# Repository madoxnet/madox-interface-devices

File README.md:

Madox-Ergonomic-Trackball
Mouse-Ergonomics-Test

|Function|Component|Module|
|---|---|---|
|Processing|ARM Cortex M4F|Adafruit Feather nRF52 Bluefruit LE |
|Power source|1000 mAh Lithium Polymer||
|Optical Sensing|Avago ADNS-9800||
|Optical Lens|Avago ADNS-6190-002||

## Design Parameters
|Parameter|Min|Nom|Max|
|---|---|---|---|
|Sensing distance|2.18mm|2.4mm|2.62|
|Bearing diameter||3mm||
|Trackball diameter||40mm||
|Handedness||Right||

## Controls
- Left Mouse Button
- Right Mouse Button
- Scroll Wheel
- Scroll Wheel Centre Mouse
- Power Switch
- ~~Scroll Wheel left right = Ctrl Tab / Ctrl Shift Tab?~~

## Target Specifications
|Parameter|Min|
|---|---|
|Ball diameter|40mm|
|Ball Material|Tiger's Eye|
|Ball Suspension|3mm Silicon Nitride (Si<sub>3</sub>N<sub>4</sub>) Round Bearings in Polycprolactone casing |
|Construction|Acrylonitrile butadiene styrene|
|Tracking Technology|Laser Optical Sensing|
|Tracking Resolution|Up to 8200 counts per inch|
|Tracking Speed|Up to 150 inches per second|

<https://en.wikipedia.org/wiki/Tiger%27s_eye>
<https://en.wikipedia.org/wiki/Silicon_nitride>

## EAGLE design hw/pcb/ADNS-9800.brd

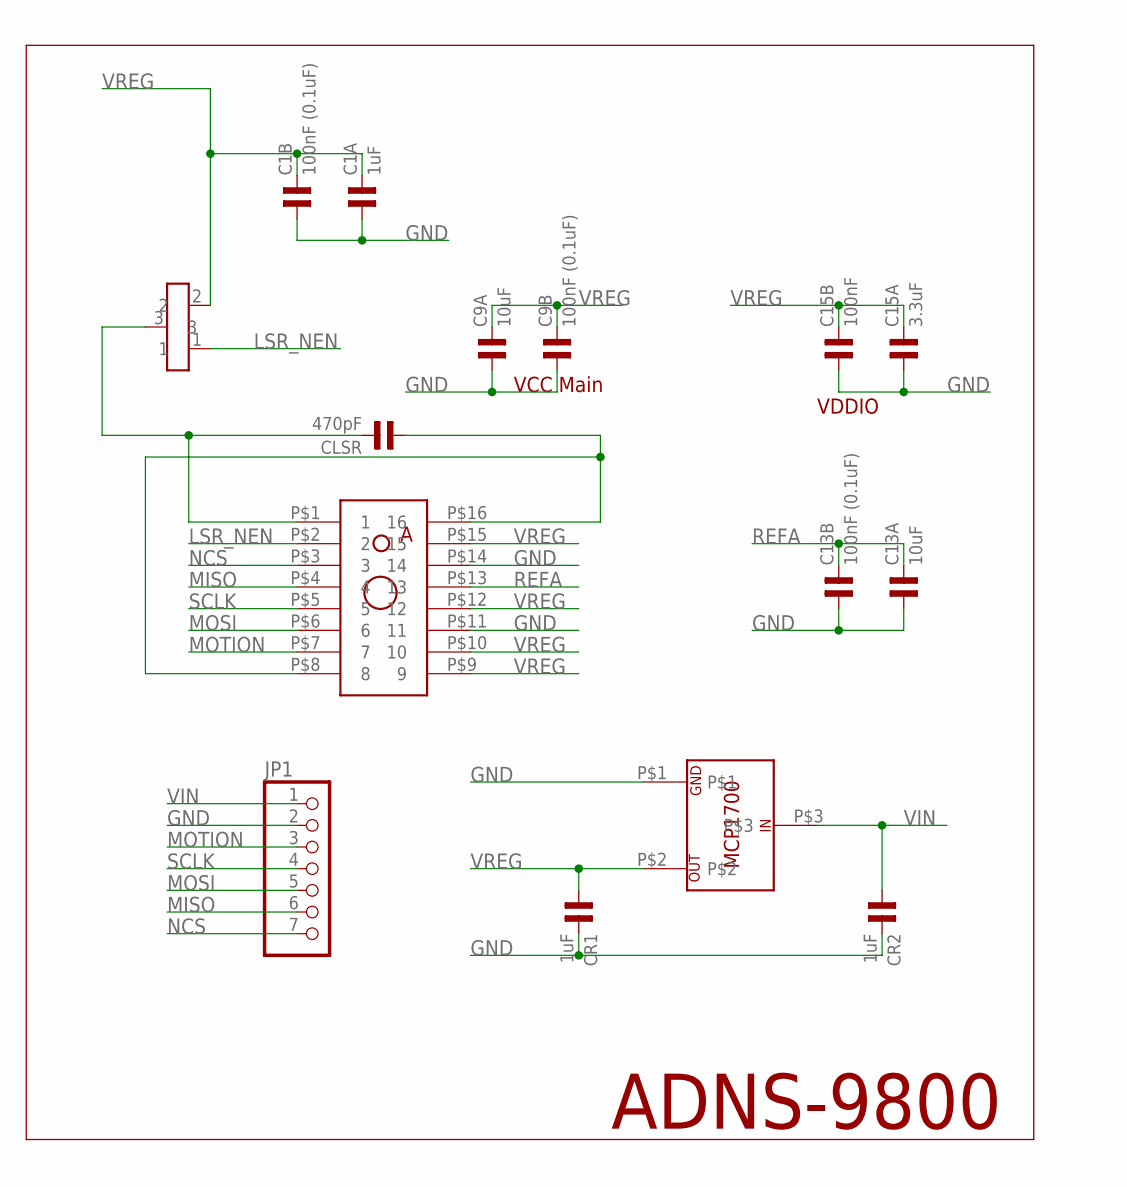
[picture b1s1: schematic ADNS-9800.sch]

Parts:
C1A: 1uF; 0603
C1B, C9B, C13B: 100nF (0.1uF); 0603
C9A, C13A: 10uF; 0603
C15A: 3.3uF; 0603
C15B: 100nF; 0603
CLSR: 470pF; 0603
CR1, CR2: 1uF; 0603
JP1: PINHD-1X7; 1X07
Q1: TRANSISTOR_SC-75; SC-75_TRANSISTOR
U$1: AVAGO_ADNS-9500
U$2: MCP1700__LDO

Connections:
CM: CLSR.2, Q1.3, U$1.P$1 (1)
GND: C1A.1, C1B.1, C9A.1, C9B.1, C13A.1, C13B.1, C15A.1, C15B.1, CR1.2, CR2.2, JP1.2, U$1.P$11 (11), U$1.P$14 (14), U$2.P$1
LSR_NEN: Q1.1, U$1.P$2 (2)
MISO: JP1.6, U$1.P$4 (4)
MOSI: JP1.5, U$1.P$6 (6)
MOTION: JP1.3, U$1.P$7 (7)
unnamed: CLSR.1, U$1.P$8 (8), U$1.P$16 (16)
NCS: JP1.7, U$1.P$3 (3)
REFA: C13A.2, C13B.2, U$1.P$13 (13)
SCLK: JP1.4, U$1.P$5 (5)
VIN: CR2.1, JP1.1, U$2.P$3
VREG: C1A.2, C1B.2, C9A.2, C9B.2, C15A.2, C15B.2, CR1.1, Q1.2, U$1.P$9 (9), U$1.P$10 (10), U$1.P$12 (12), U$1.P$15 (15), U$2.P$2

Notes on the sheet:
ADNS-9800
VDDIO
VCC Main

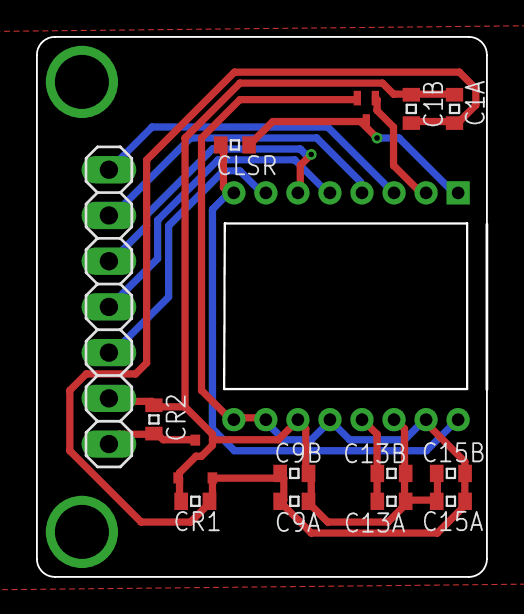
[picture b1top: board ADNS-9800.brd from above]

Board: 2 copper layers, 25.0 x 29.9 mm, 15 parts (0 on the bottom side), 12 nets.

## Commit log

2017-06-18 :circus_tent: Added .gitattributes & .gitignore files
2017-06-18 Initial Commit
    PCB and Test STL files
2017-06-18 Fix readme
2017-06-22 Initial Gerbers
